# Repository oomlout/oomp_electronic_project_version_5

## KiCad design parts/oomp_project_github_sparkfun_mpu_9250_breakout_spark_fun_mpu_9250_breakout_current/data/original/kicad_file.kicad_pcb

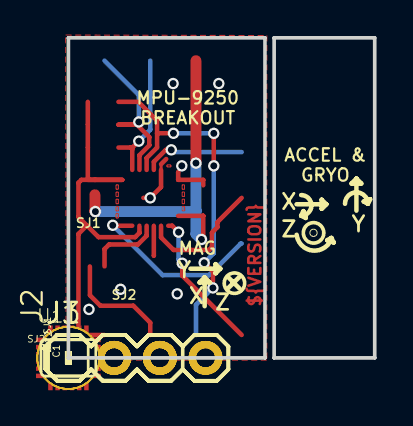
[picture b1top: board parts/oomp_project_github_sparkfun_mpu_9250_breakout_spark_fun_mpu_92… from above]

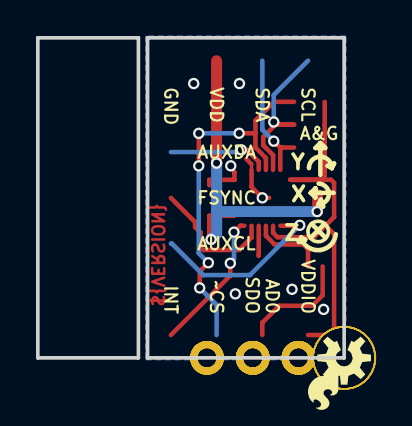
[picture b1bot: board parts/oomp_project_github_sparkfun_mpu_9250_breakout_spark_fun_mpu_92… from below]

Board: 2 copper layers, 17.0 x 17.8 mm, 18 parts (2 on the bottom side), 13 nets.

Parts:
C1, C2: 0.1uF; 0603-CAP
FID1, FID2: FIDUCIAL1X2; FIDUCIAL-1X2
FRAME1: FRAME-LETTER; CREATIVE_COMMONS
J1, J3: 1X04
J2: 1X03
LOGO1: SFE_LOGO_FLAME.1_INCH; SFE_LOGO_FLAME_.1
LOGO2: OSHW-LOGOS; OSHW-LOGO-S
R1, R2, R3: 10K; 0603-RES
SJ1: JUMPER-PAD-2-NC_BY_PASTEFULL-BOX-SILK; PAD-JUMPER-2-NC_BY_PASTE_YES_SILK_FULL_BOX
SJ2: JUMPER_PAD-3-1&2_NC_BY_PASTE; PAD-HUMPER-3-1&2_NC_BY_PASTE_YES_SILK_FULL_BOX
STANDOFF1, STANDOFF2: STAND-OFF
U1: MPU-9250; QFN24_PAD

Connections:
AD0/SDO: J3.2, SJ2.3
ADSD_STUB: SJ2.2, U1.9
AUX_CL: J2.1, U1.7
AUX_DA: J2.3, U1.21
FSYNC: J2.2, U1.11
GND: C1.2, C2.2, J1.4, SJ2.1, U1.18, U1.20, U1.CENTER
INT: J3.4, U1.12
REGOUT: C1.1, U1.10
SCL/SCLK: J1.1, R2.1, U1.23
SDA/SDI: J1.2, R1.1, U1.24
VDD: C2.1, J1.3, SJ1.1, U1.13
VDDIO: J3.1, R1.2, R2.2, R3.2, SJ1.2, U1.1, U1.8
~CS: J3.3, R3.1, U1.22

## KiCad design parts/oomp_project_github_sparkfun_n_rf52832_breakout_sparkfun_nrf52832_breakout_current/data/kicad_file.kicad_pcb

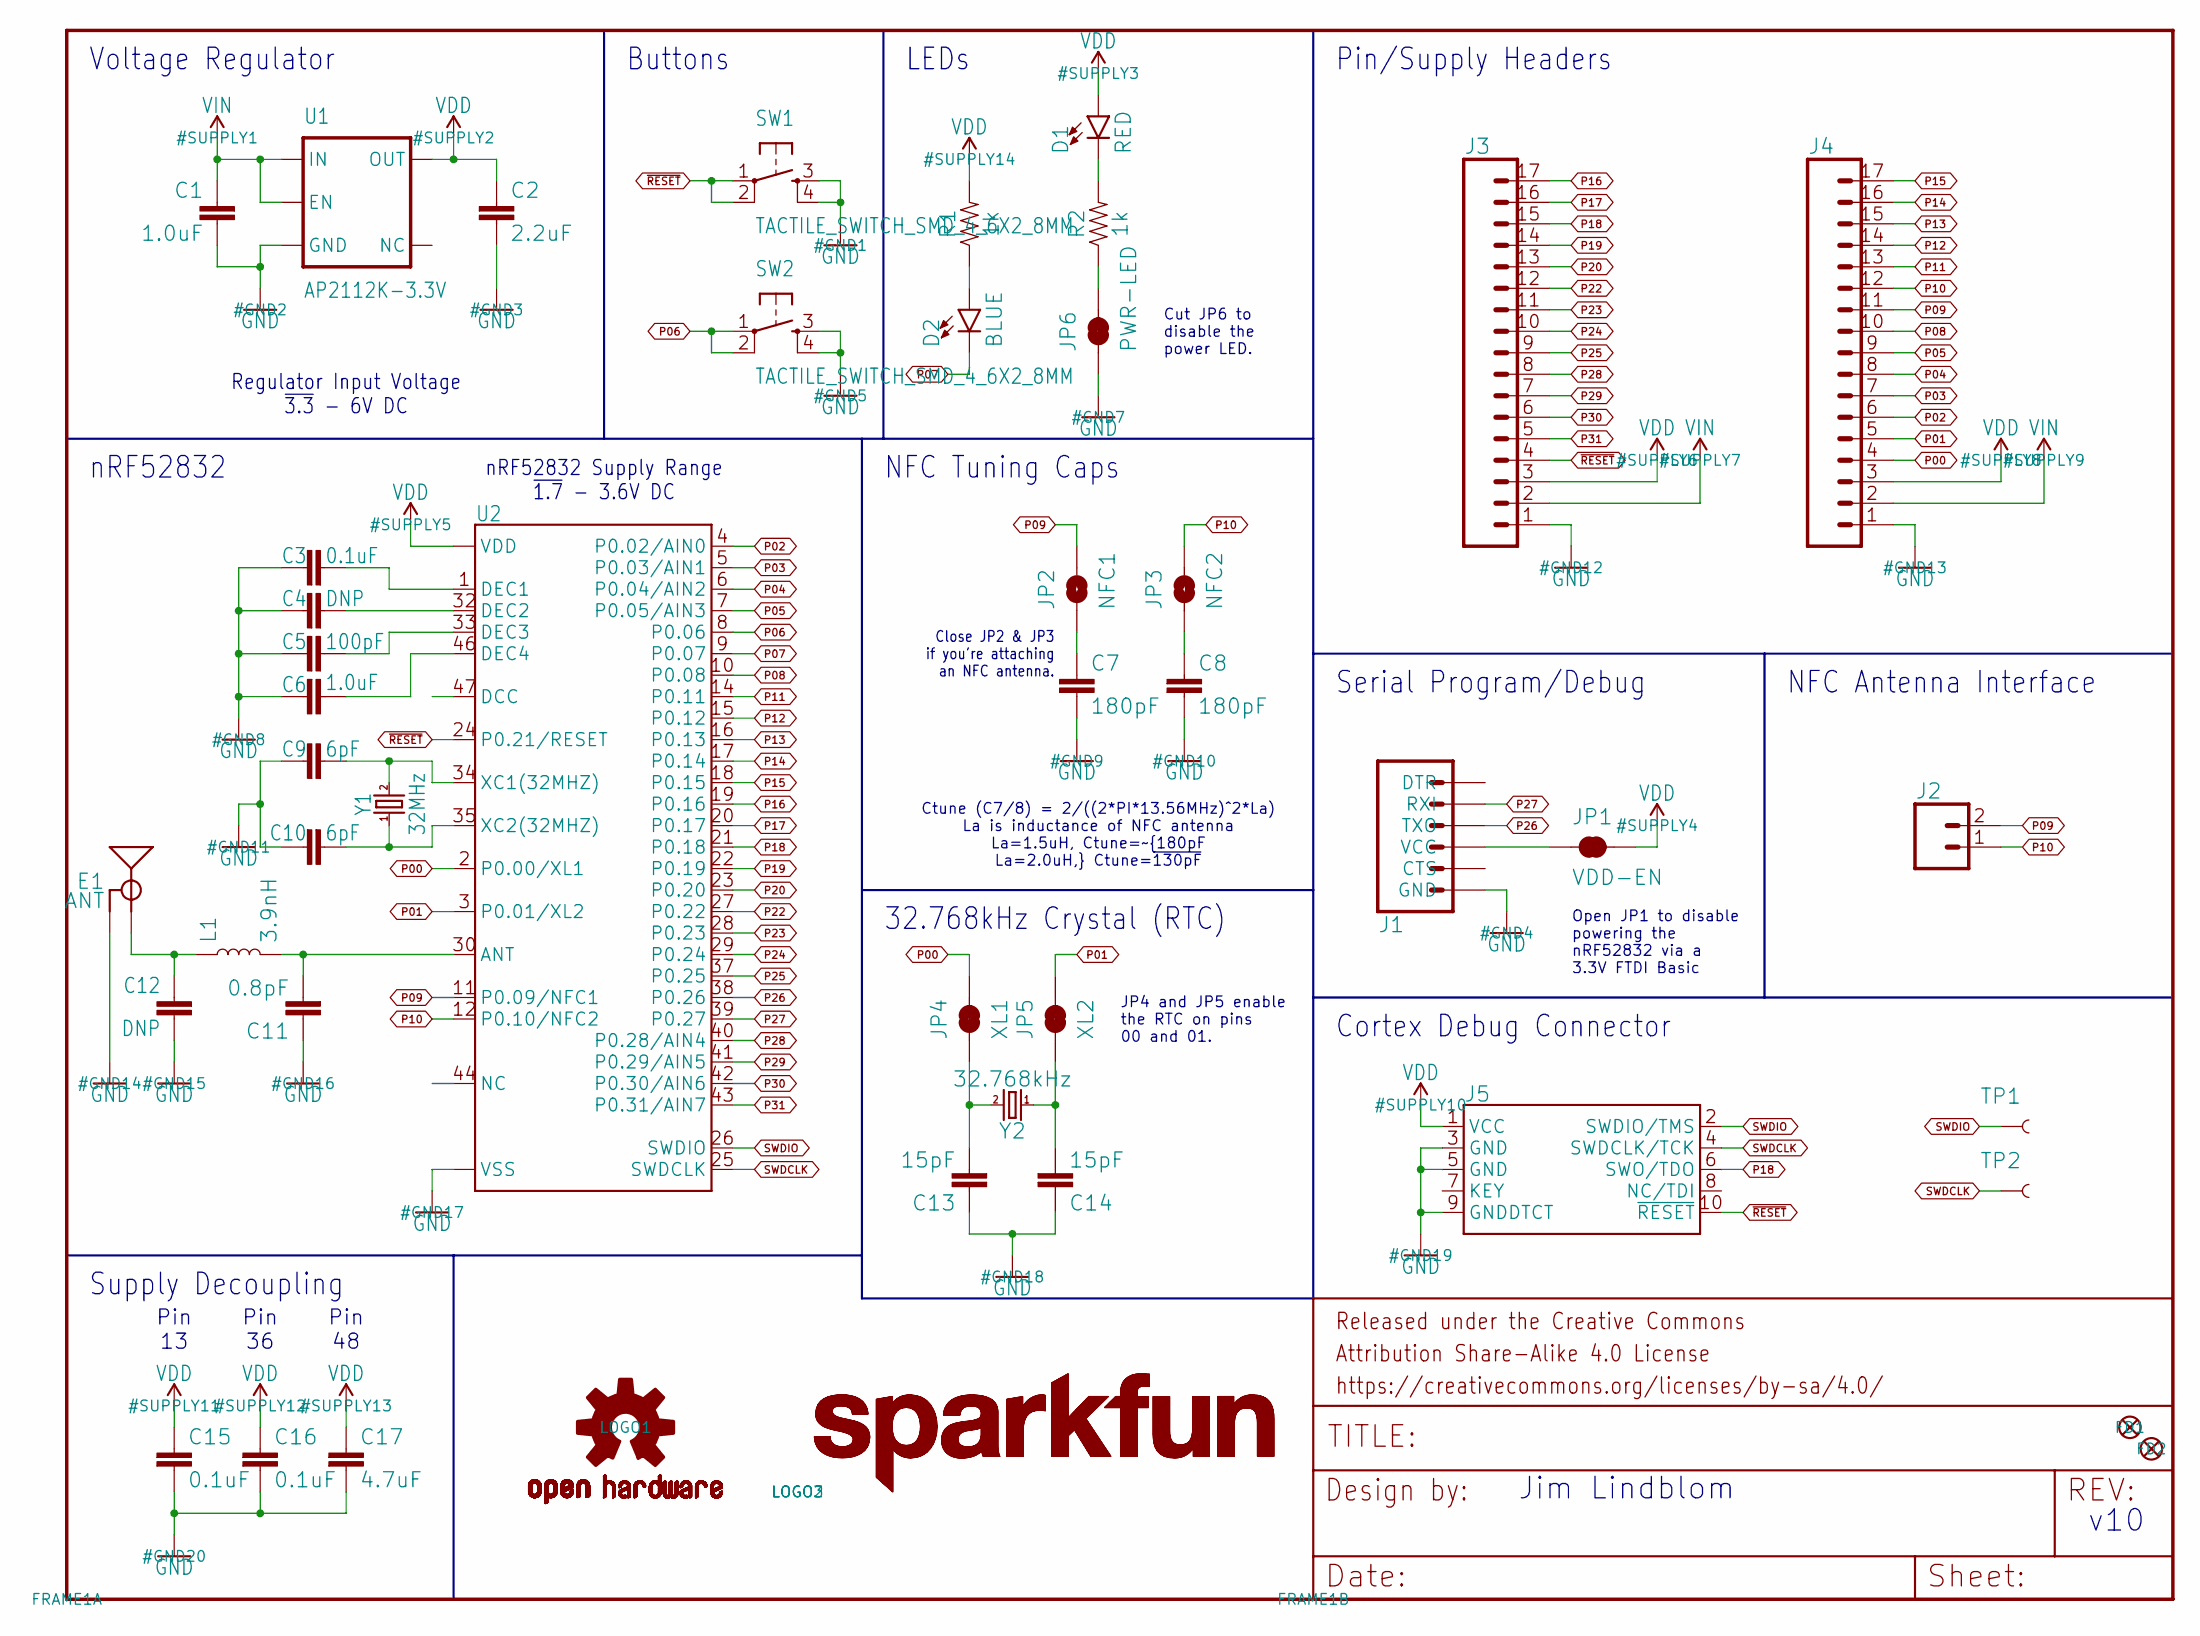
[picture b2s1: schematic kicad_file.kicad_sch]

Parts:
C1: 1.0uF; 0603
C2: 2.2uF; 0603
C3, C15, C16: 0.1uF; 0402
C4, C12: DNP; 0402
C5: 100pF; 0402
C6: 1.0uF; 0402
C7, C8: 180pF; 0603
C9, C10: 6pF; 0402
C11: 0.8pF; 0402
C13, C14: 15pF; 0402
C17: 4.7uF; 0603
D1: RED; LED-0603
D2: BLUE; LED-0603
E1: ANT; TRACE_ANTENNA_2.4GHZ_15.2MM
FD1, FD2: FIDUCIALUFIDUCIAL; FIDUCIAL-MICRO
FRAME1: FRAME-LETTER; CREATIVE_COMMONS
J1: ARDUINO_SERIAL_PROGRAMPTH; 1X06
J2: CONN_02PTH; 1X02
J3, J4: CONN_17; 1X17
J5: CORTEX_DEBUGPTH; 2X5-PTH-1.27MM
JP1: VDD-EN; SMT-JUMPER_2_NC_TRACE_SILK
JP2: NFC1; SMT-JUMPER_2_NO_SILK
JP3: NFC2; SMT-JUMPER_2_NO_SILK
JP4: XL1; PAD-JUMPER-2-NC_BY_TRACE_YES_SILK
JP5: XL2; PAD-JUMPER-2-NC_BY_TRACE_YES_SILK
JP6: PWR-LED; PAD-JUMPER-2-NC_BY_TRACE_YES_SILK
L1: 3.9nH; 0402
LOGO1: OSHW-LOGOMINI; OSHW-LOGO-MINI
LOGO2, LOGO3: SFE_LOGO_NAME.1_INCH; SFE_LOGO_NAME_.1
R1, R2: 1k; 0603
SW1, SW2: TACTILE_SWITCH_SMD_4_6X2_8MM; TACTILE_SWITCH_SMD_4.6X2.8MM
TP1, TP2: TEST-POINT3X4; PAD.03X.04
U1: AP2112K-3.3V; SOT23-5
U2: NRF52832; QFN48-6X6MM
Y1: 32MHz; CRYSTAL-SMD-2.0X1.6MM
Y2: 32.768kHz; CRYSTAL-SMD-3.2X1.5MM

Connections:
ANT: C11.2, L1.2, U2.30 (ANT)
DCC: U2.47 (DCC)
DEC1: C3.2, U2.1 (DEC1)
DEC2: C4.2, U2.32 (DEC2)
DEC3: C5.2, U2.33 (DEC3)
DEC4: C6.2, U2.46 (DEC4)
GND: C1.2, C2.2, C3.1, C4.1, C5.1, C6.1, C7.2, C8.2, C9.1, C10.2, C11.1, C12.2, C13.1, C14.1, C15.2, C16.2, C17.2, E1.GND, J1.6 (GND), J3.1, J4.1, J5.3 (GND), J5.5 (GND), J5.9 (GNDDTCT), JP6.1, SW1.3, SW1.4, SW2.3, SW2.4, U1.2 (GND), U2.31 (VSS), U2.45 (VSS), U2.EP (VSS)
unnamed: JP6.2, R2.1
unnamed: C13.2, JP4.1, Y2.P$2 (2)
unnamed: C14.2, JP5.1, Y2.P$1 (1)
unnamed: C12.1, E1.ANT (SIGNAL), L1.1
unnamed: D1.C, R2.2
unnamed: J1.4 (VCC), JP1.1
unnamed: D2.A, R1.1
NC: U2.44 (NC)
NFC1: C7.1, JP2.1
NFC2: C8.1, JP3.1
P00: J4.4, JP4.2, U2.2 (P0.00/XL1)
P01: J4.5, JP5.2, U2.3 (P0.01/XL2)
P02: J4.6, U2.4 (P0.02/AIN0)
P03: J4.7, U2.5 (P0.03/AIN1)
P04: J4.8, U2.6 (P0.04/AIN2)
P05: J4.9, U2.7 (P0.05/AIN3)
P06: SW2.1, SW2.2, U2.8 (P0.06)
P07: D2.C, U2.9 (P0.07)
P08: J4.10, U2.10 (P0.08)
P09: J2.2, J4.11, JP2.2, U2.11 (P0.09/NFC1)
P10: J2.1, J4.12, JP3.2, U2.12 (P0.10/NFC2)
P11: J4.13, U2.14 (P0.11)
P12: J4.14, U2.15 (P0.12)
P13: J4.15, U2.16 (P0.13)
P14: J4.16, U2.17 (P0.14)
P15: J4.17, U2.18 (P0.15)
P16: J3.17, U2.19 (P0.16)
P17: J3.16, U2.20 (P0.17)
P18: J3.15, J5.6 (SWO/TDO), U2.21 (P0.18)
P19: J3.14, U2.22 (P0.19)
P20: J3.13, U2.23 (P0.20)
P22: J3.12, U2.27 (P0.22)
P23: J3.11, U2.28 (P0.23)
P24: J3.10, U2.29 (P0.24)
P25: J3.9, U2.37 (P0.25)
P26: J1.3 (TXO), U2.38 (P0.26)
P27: J1.2 (RXI), U2.39 (P0.27)
P28: J3.8, U2.40 (P0.28/AIN4)
P29: J3.7, U2.41 (P0.29/AIN5)
P30: J3.6, U2.42 (P0.30/AIN6)
P31: J3.5, U2.43 (P0.31/AIN7)
SWDCLK: J5.4 (SWDCLK/TCK), TP2.P$1, U2.25 (SWDCLK)
SWDIO: J5.2 (SWDIO/TMS), TP1.P$1, U2.26 (SWDIO)
VDD: C2.1, C15.1, C16.1, C17.1, D1.A, J3.3, J4.3, J5.1 (VCC), JP1.2, R1.2, U1.5 (OUT), U2.13 (VDD), U2.36 (VDD), U2.48 (VDD)
VIN: C1.1, J3.2, J4.2, U1.1 (IN), U1.3 (EN)
XC1: C9.2, U2.34 (XC1(32MHZ)), Y1.3 (2)
XC2: C10.1, U2.35 (XC2(32MHZ)), Y1.1
~RESET: J3.4, J5.10 (~RESET), SW1.1, SW1.2, U2.24 (P0.21/RESET)

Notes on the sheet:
Pin 48
NFC Tuning Caps
Ctune (C7/8) = 2/((2*PI*13.56MHz)^2*La) La is inductance of NFC antenna La=1.5uH, Ctune=~{180pF La=2.0uH,} Ctune=~{130pF}
32.768kHz Crystal (RTC)
Jim Lindblom
Cortex Debug Connector
Close JP2 & JP3 if you're attaching an NFC antenna.
Pin 36
LEDs
Supply Decoupling
nRF52832 Supply Range ~{1.7} - 3.6V DC~{}
Voltage Regulator
Pin 13
Serial Program/Debug
Buttons
v10
Open JP1 to disable powering the nRF52832 via a 3.3V FTDI Basic
Cut JP6 to disable the power LED.
nRF52832
JP4 and JP5 enable the RTC on pins 00 and 01.
Regulator Input Voltage ~{3.3} - 6V DC~{}
Pin/Supply Headers
NFC Antenna Interface

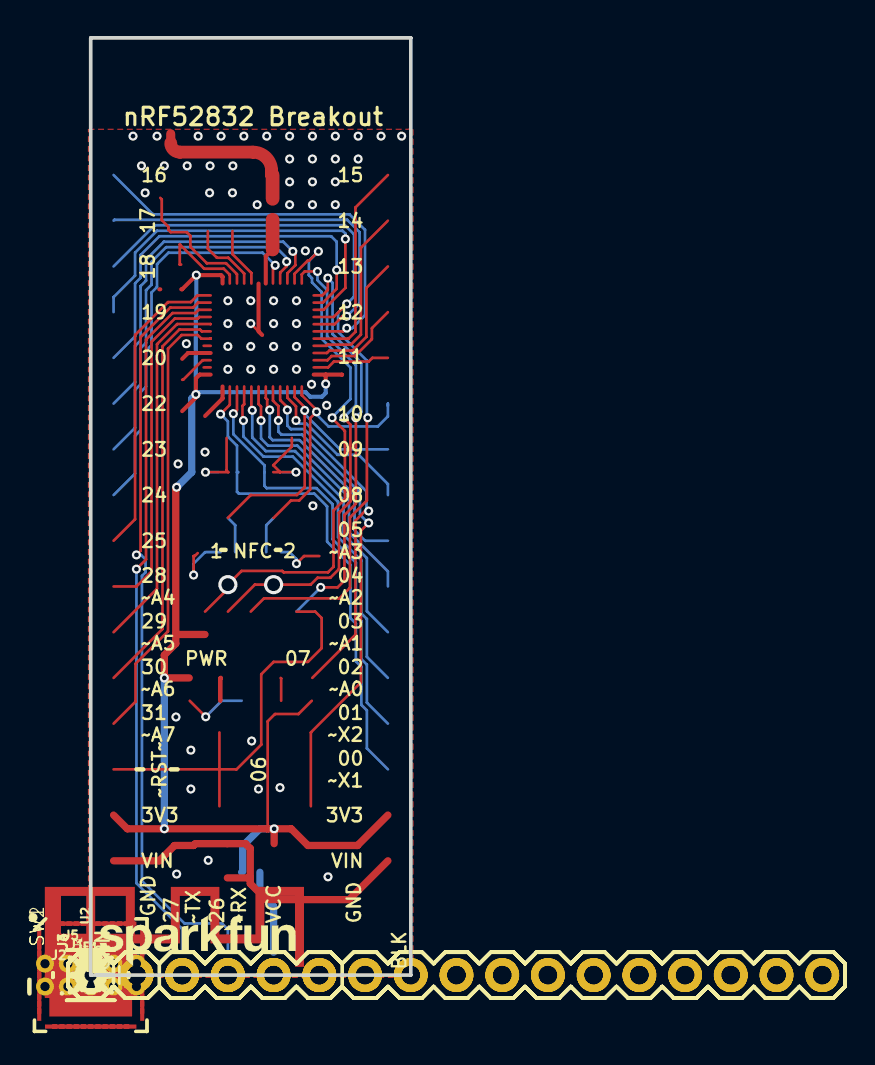
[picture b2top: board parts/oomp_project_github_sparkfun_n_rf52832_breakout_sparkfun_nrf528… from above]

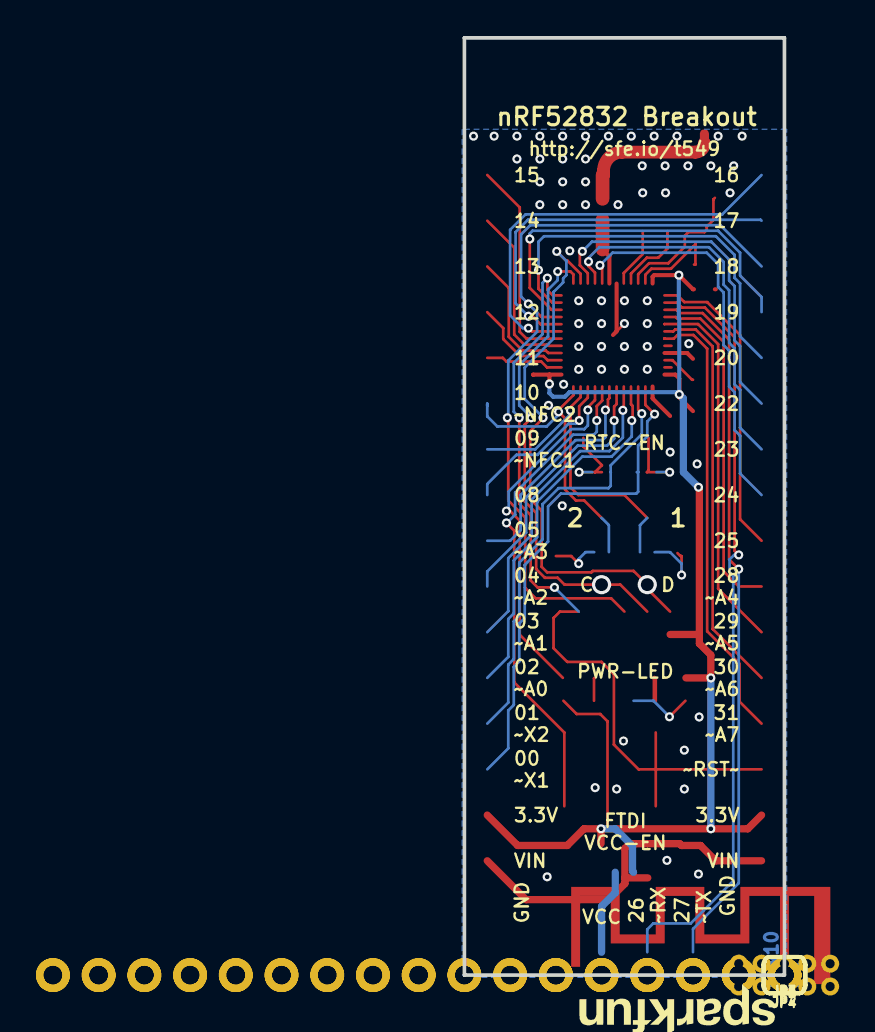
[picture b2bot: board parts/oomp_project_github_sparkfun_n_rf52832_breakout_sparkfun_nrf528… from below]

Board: 2 copper layers, 17.8 x 52.1 mm, 48 parts (9 on the bottom side), 53 nets.

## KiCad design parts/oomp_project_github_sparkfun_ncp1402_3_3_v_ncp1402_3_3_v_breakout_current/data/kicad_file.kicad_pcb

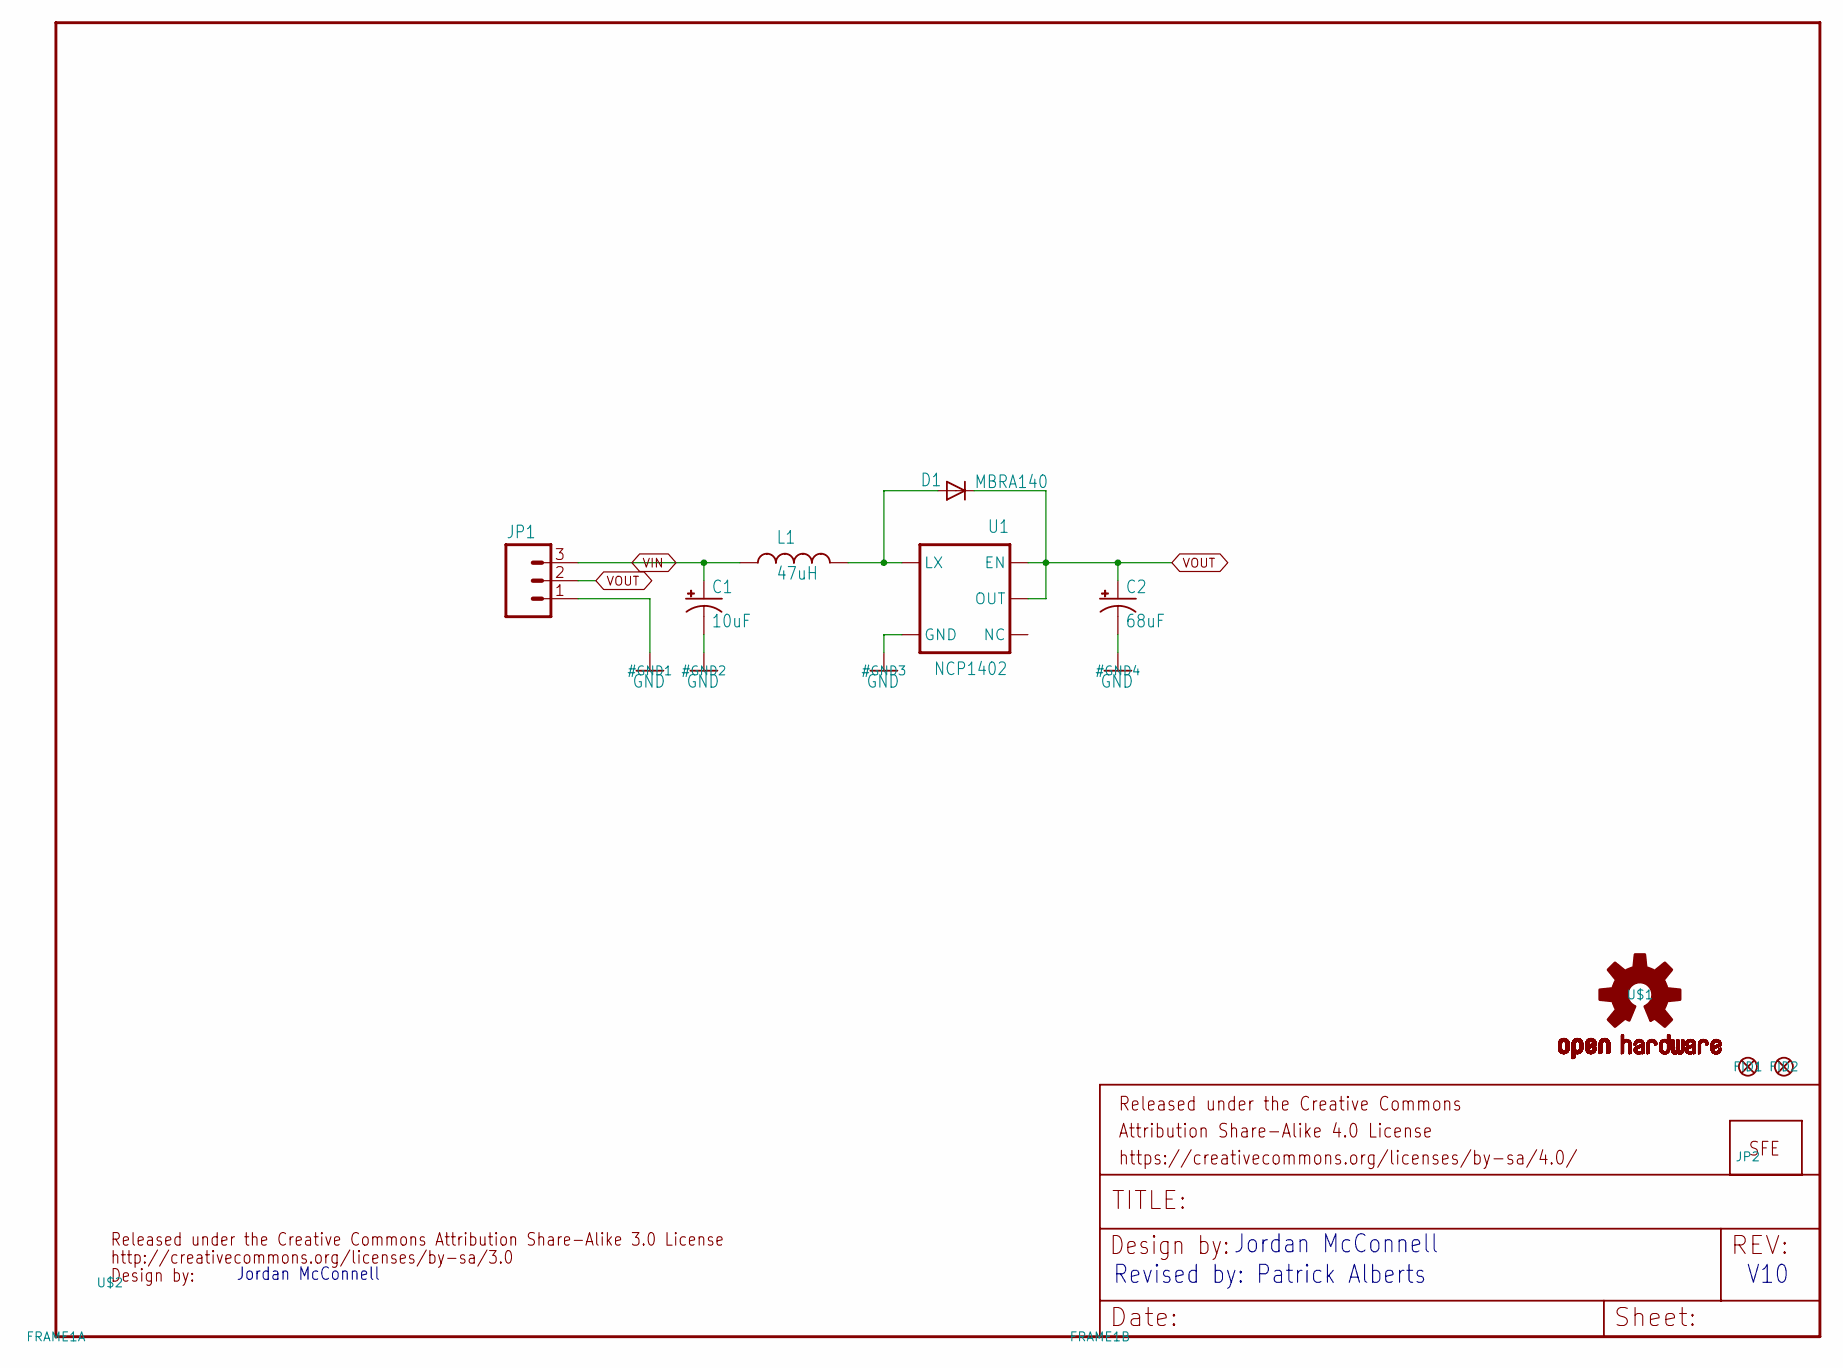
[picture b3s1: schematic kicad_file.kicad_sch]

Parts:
C1: 10uF; EIA3216
C2: 68uF; EIA3528
D1: MBRA140; SMA-DIODE
FID1, FID2: FIDUCIAL1X2; FIDUCIAL-1X2
FRAME1: FRAME-LETTER; CREATIVE_COMMONS
JP1: M03PTH; 1X03
JP2: LOGO-SFESK; SFE-LOGO-FLAME
L1: 47uH; CR54
U1: NCP1402; SOT23-5
U$1: OSHW-LOGOS; OSHW-LOGO-S
U$2: CREATIVE_COMMONS

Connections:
GND: C1.C (-), C2.C (-), JP1.1, U1.4 (GND)
unnamed: D1.A, L1.P$2 (2), U1.5 (LX)
VIN: C1.A (+), JP1.3, L1.P$1 (1)
VOUT: C2.A (+), D1.C, JP1.2, U1.1 (EN), U1.2 (OUT)

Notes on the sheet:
V10
Revised by: Patrick Alberts
Jordan McConnell

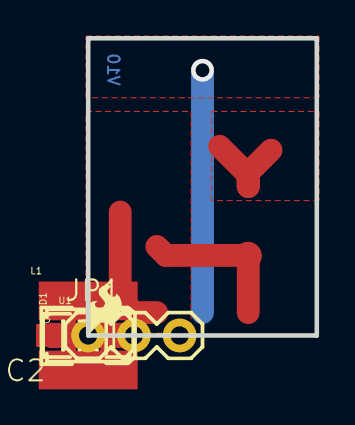
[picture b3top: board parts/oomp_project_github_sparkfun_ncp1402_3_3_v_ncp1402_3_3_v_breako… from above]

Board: 2 copper layers, 12.7 x 16.5 mm, 12 parts (1 on the bottom side), 4 nets.

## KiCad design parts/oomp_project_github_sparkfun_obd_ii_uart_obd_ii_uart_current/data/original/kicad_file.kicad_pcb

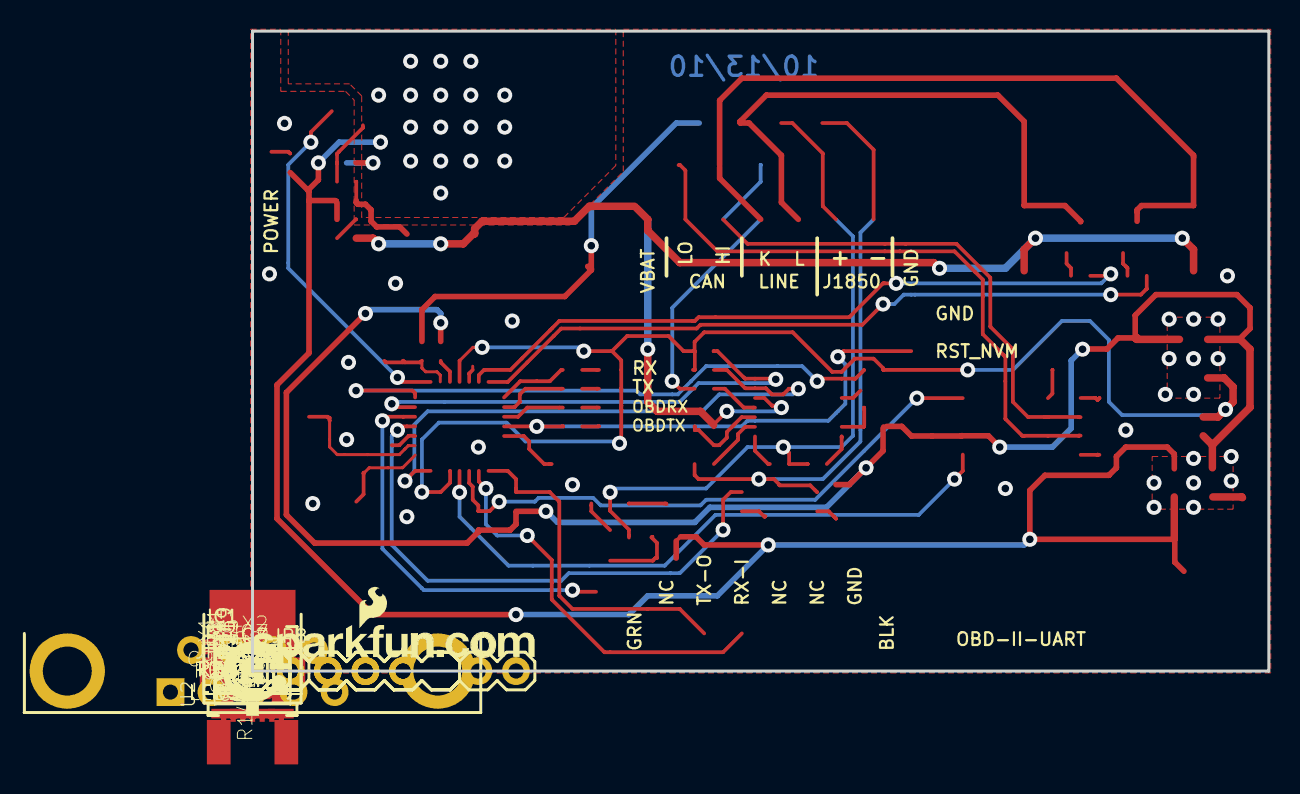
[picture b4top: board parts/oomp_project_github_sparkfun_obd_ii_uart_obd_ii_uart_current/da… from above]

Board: 2 copper layers, 68.6 x 43.2 mm, 88 parts (0 on the bottom side), 57 nets.

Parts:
C1, C5, C6, C11, C17: 1uF; 0402-CAP
C2, C3: 27pF; 0402-CAP
C4: 10uF ESR<=5; EIA3216
C7, C10, C14: 0.1uF; 0402-CAP
C8: 4.7uF; 0402-CAP
C9, C18: 10uF; EIA3216
C12, C13: 560pF; 0402-CAP
C15: 2.2uF; 0402-CAP
C16: 470pF; 0402-CAP
D1, D2, D3: BAS16; SOD-323
D4: MBRA140; SMA-DIODE
IC1: SCANTOOL; _STN_SCANTOOL_QFN-28-S
IC3: LM339PWR; TSSOP-14
IC4: MCP2551; SO-8
JP1: 1X08
JP2, JP10: FIDUCIAL1X2; FIDUCIAL-1X2
JP3: LOGO-SFENEW; SFE-NEW-WEBLOGO
JP4, JP5, JP6, JP7: STAND-OFF
JP8: DNP; FTDI_BASIC
JP9: DNP; 1X02
LED1, LED3: YELLOW; LED-0603
LED2, LED4, LED5: RED; LED-0603
Q3, Q4, Q8: MMBT2222; SOT23-3
Q7: ZXMP6A13FTA; SOT23
Q9, Q10: BSS138; SOT23-3
R1, R9, R10, R12, R18, R21, R27, R28, R29, R30, R31, R33: 10k; 0402-RES
R2, R7, R13, R32: 1k; 0402-RES
R3: 62K; 0402-RES
R4, R5, R35, R37: 330; 0402-RES
R6: 10K; 0402-RES
R8, R11: 510 0.5W; 2010
R14, R15: 100; 0402-RES
R16, R23, R25: 4.7k; 0402-RES
R17: 1.2k; 0402-RES
R19: 866; 0402-RES
R20: 240; 0402-RES
R22: 374; 0402-RES
R24, R34: 1.5k; 0402-RES
U1: 3.3V; SOT23-5
U2: V_REG_317DPACK; V-REG_DPACK
U3: 5V Reg.; SOT23-5
U$1: CREATIVE_COMMONS
U$14: OSHW-LOGO
X2: Male DB9; DB9_MALE
Y1: 16MHz; CRYSTAL-SMD-5X3

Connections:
3.3V: C1.1, C5.1, C8.1, IC1.10, IC1.25, LED1.A, LED2.A, LED3.A, LED4.A, R9.2, R18.2, R27.2, U1.5
5V: C6.1, C11.1, C15.1, C18.A, D3.2, IC4.3, R1.2, R17.2, R25.1, R34.1, U1.1, U1.3, U3.5
BATT_V: C7.1, IC1.27, R3.1, R6.2
CAN_HI: IC4.7, JP1.6, R14.2, X2.3
CAN_LO: IC4.6, JP1.7, R15.2, X2.5
CAN_RX: IC1.11, IC4.4
CAN_TX: IC1.12, IC4.1, R34.2
GND: C1.2, C2.2, C3.2, C4.C, C5.2, C6.2, C7.2, C8.2, C9.C, C10.2, C11.2, C12.2, C13.2, C14.2, C15.2, C16.2, C17.2, C18.C, D2.1, IC1.5, IC1.16, IC1.24, IC1.EXP, IC3.12, IC4.2, JP1.1, JP8.GND, JP9.2, LED5.C, Q3.2, Q4.2, Q8.2, Q9.2, Q10.2, R6.1, R16.1, R22.1, R23.1, R33.2, U1.2, U3.2, X2.1, X2.2
J1850BUS+: D1.1, JP1.3, R21.1, R28.1, R30.1, X2.7
J1850BUS+_TX: IC1.3, Q9.1
J1850BUS-: JP1.2, Q8.3, R29.1, R31.2, X2.6
J1850BUS-_TX: IC1.4, R32.1
K-LINE: JP1.5, Q4.3, R11.2, R12.1, X2.4
L-LINE: JP1.4, Q3.3, R8.2, X2.8
unnamed: IC3.7, R28.2
unnamed: IC3.6, R29.2
unnamed: Q4.1, R13.1
unnamed: Q3.1, R7.1
unnamed: IC3.5, R10.2, R33.1
unnamed: IC3.8, R21.2
unnamed: R19.2, R20.2, U2.1
unnamed: D1.2, Q7.3
unnamed: C12.1, R14.1
unnamed: IC4.8, R16.2
unnamed: IC3.9, R17.1, R23.2
unnamed: IC3.4, R12.2
unnamed: D3.1, R31.1
unnamed: Q7.1, Q9.3, R24.2
unnamed: Q10.3, R19.1, R22.2
unnamed: D2.2, R30.2
unnamed: Q8.1, R32.2
unnamed: C4.A, IC1.17
unnamed: C13.1, R15.1
unnamed: LED3.C, R4.2
unnamed: LED4.C, R5.1
unnamed: LED5.A, R2.1
unnamed: C16.1, U3.4
unnamed: LED1.C, R35.2
unnamed: LED2.C, R37.1
OSC1: C2.1, IC1.6, Y1.3
OSC2: C3.1, IC1.7, Y1.1
PWM/~VPW: IC1.28, Q10.1
PWM_RX: IC1.2, IC3.1, R27.1
RESET: IC1.26, R1.1
RST_NVM: IC1.18, JP9.1, R5.2
RX-I: IC1.13, JP8.TXO
RX-STAT: IC1.21, R35.1
TX-O: IC1.14, JP8.RXI, R25.2
TX-STAT: IC1.20, R37.2
VBAT: C14.1, D4.C, IC3.3, JP1.8, R8.1, R10.1, R11.1, U2.3
VBATT_RAW: D4.A, R3.2, X2.9
VCC: C9.A, C10.1, C17.1, Q7.2, R2.2, R20.1, R24.1, U2.4, U3.1, U3.3
~ISO_K_TX: IC1.22, R13.2
~ISO_L_TX: IC1.23, R7.2
~ISO_RX: IC1.8, IC3.2, R9.1
~OBD_RX_STATUS/PGC: IC1.19, R4.1
~VPW_RX: IC1.1, IC3.14, R18.1

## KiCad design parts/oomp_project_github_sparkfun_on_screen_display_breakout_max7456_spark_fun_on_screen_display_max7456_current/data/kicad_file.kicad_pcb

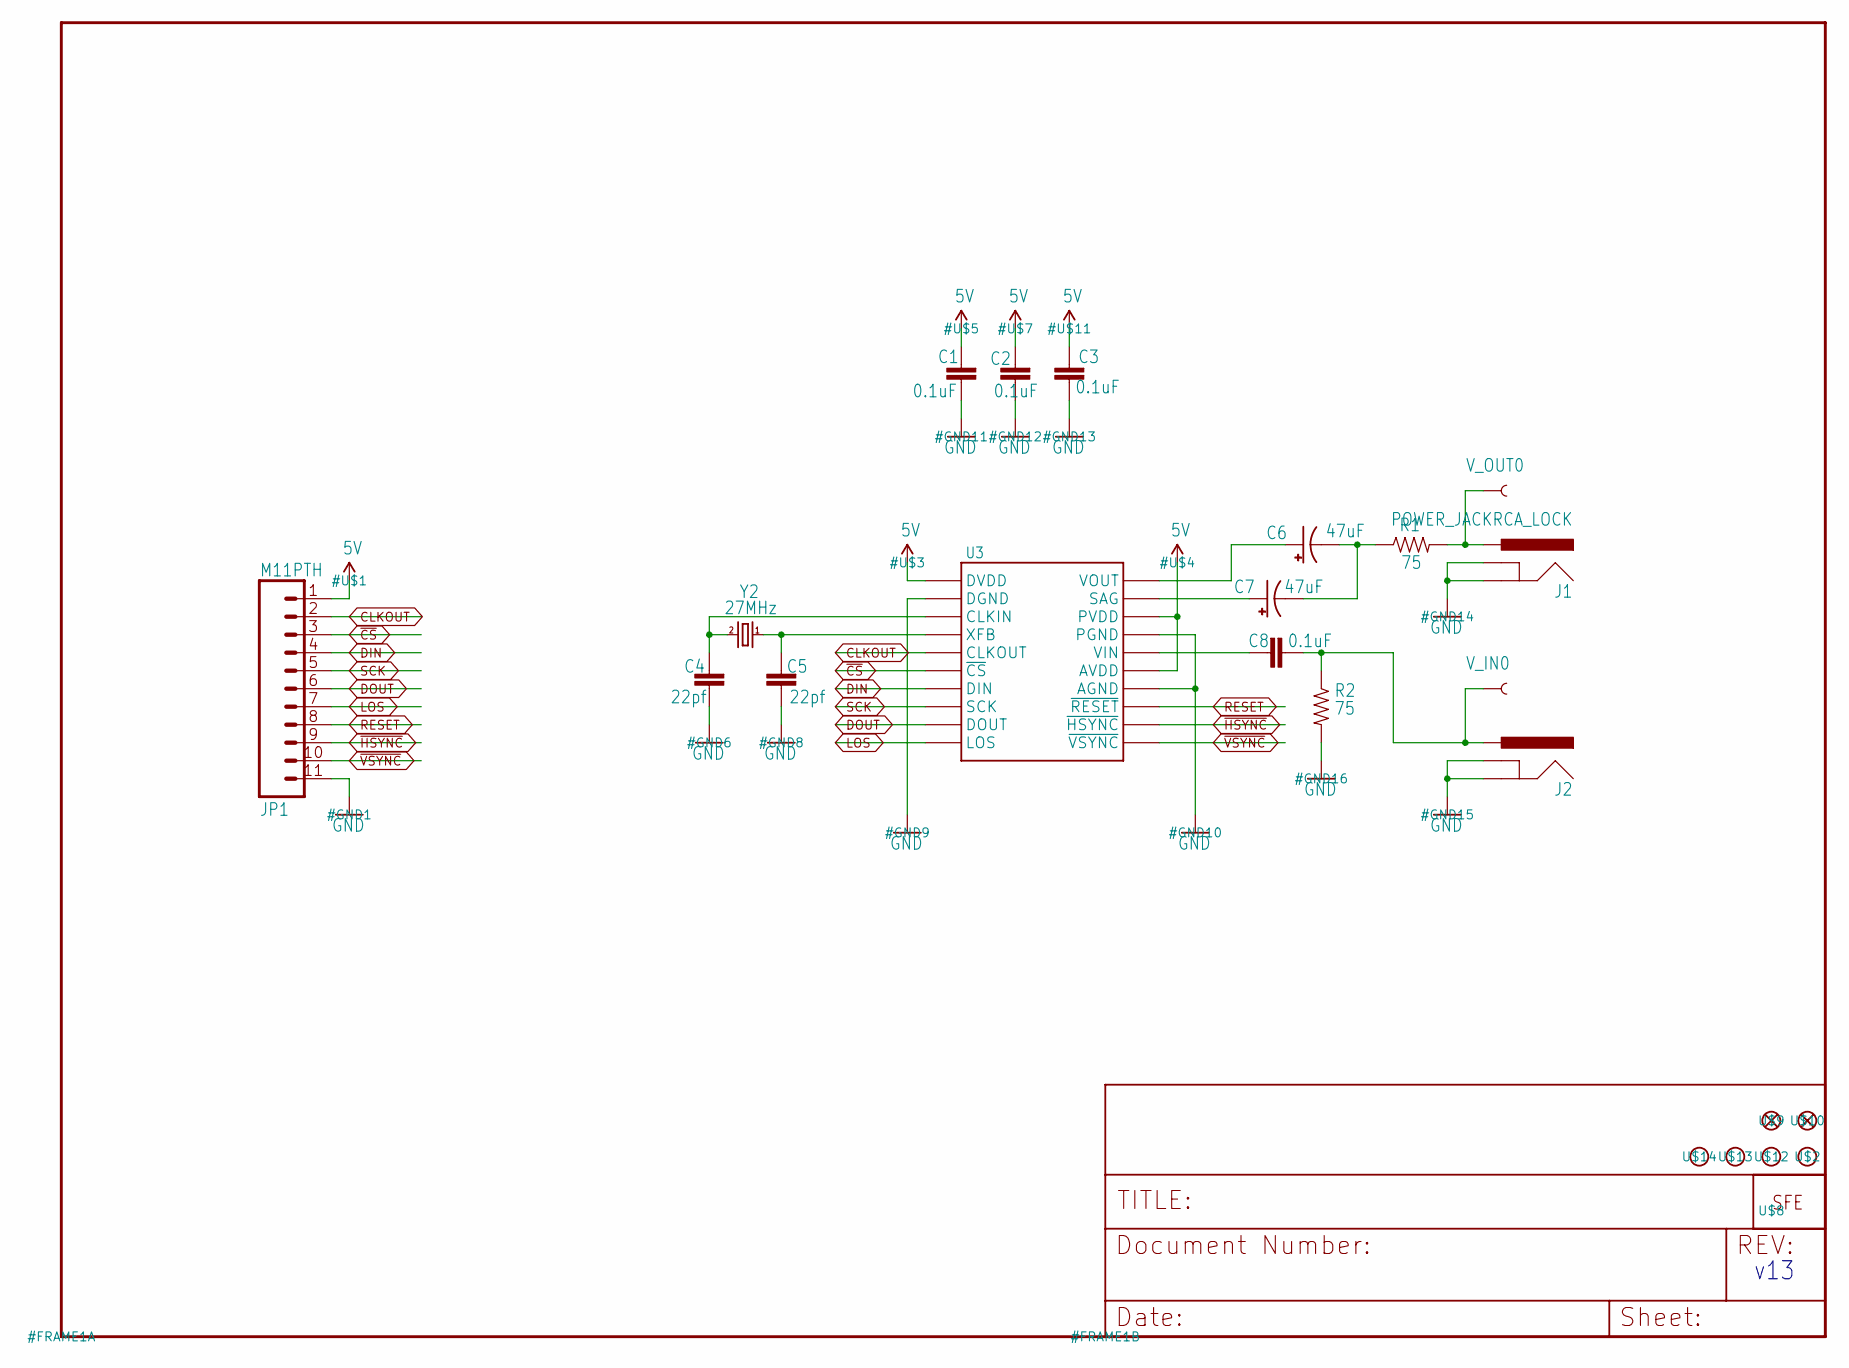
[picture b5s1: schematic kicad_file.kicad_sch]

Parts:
C1, C2, C3, C8: 0.1uF; C0402
C4, C5: 22pf; C0402
C6, C7: 47uF; EIA3528
J1, J2: POWER_JACKRCA_LOCK; RCA_LOCK
JP1: M11PTH; 1X11
R1, R2: 75; C0402
U3: MAX7456; TSSOP28
U$2, U$12, U$13, U$14: STAND-OFF
U$8: LOGO-SFENEW; SFE-NEW-WEBLOGO
U$9, U$10: FIDUCIAL1X2; FIDUCIAL-1X2
V_IN0: TEST-POINT3X5; PAD.03X.05
V_OUT0: TEST-POINT3X5; PAD.03X.05
Y2: 27MHz; CRYSTAL-SMD-5X3

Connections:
5V: C1.2, C2.2, C3.2, JP1.1, U3.3 (DVDD), U3.21 (AVDD), U3.24 (PVDD)
CLKOUT: JP1.2, U3.7 (CLKOUT)
DIN: JP1.4, U3.9 (DIN)
DOUT: JP1.6, U3.11 (DOUT)
GND: C1.1, C2.1, C3.1, C4.1, C5.1, J1.BARREL (GND), J1.SPRING (GNDBREAK), J2.BARREL (GND), J2.SPRING (GNDBREAK), JP1.11, R2.2, U3.4 (DGND), U3.20 (AGND), U3.23 (PGND)
LOS: JP1.7, U3.12 (LOS)
unnamed: C4.2, U3.5 (CLKIN), Y2.3 (2)
unnamed: C5.2, U3.6 (XFB), Y2.1
unnamed: C6.C (-), C7.C (-), R1.1
unnamed: C7.A (+), U3.25 (SAG)
unnamed: C6.A (+), U3.26 (VOUT)
unnamed: J1.BREAK (PWR), R1.2, V_OUT0.P$1
unnamed: C8.2, U3.22 (VIN)
unnamed: C8.1, J2.BREAK (PWR), R2.1, V_IN0.P$1
RESET: JP1.8, U3.19 (~RESET)
SCK: JP1.5, U3.10 (SCK)
~CS: JP1.3, U3.8 (~CS)
~HSYNC: JP1.9, U3.18 (~HSYNC)
~VSYNC: JP1.10, U3.17 (~VSYNC)

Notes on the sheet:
v13

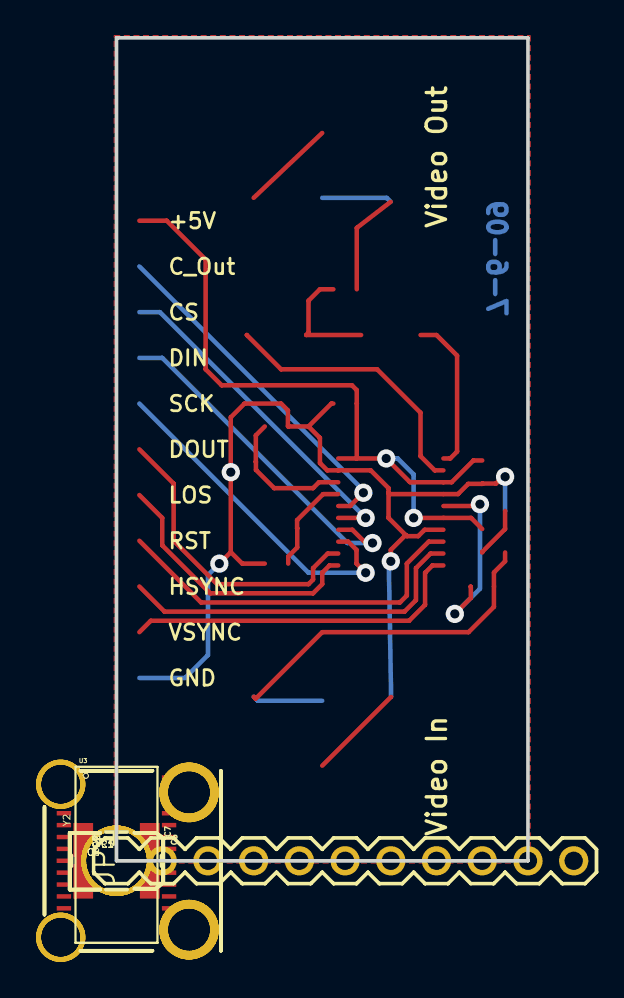
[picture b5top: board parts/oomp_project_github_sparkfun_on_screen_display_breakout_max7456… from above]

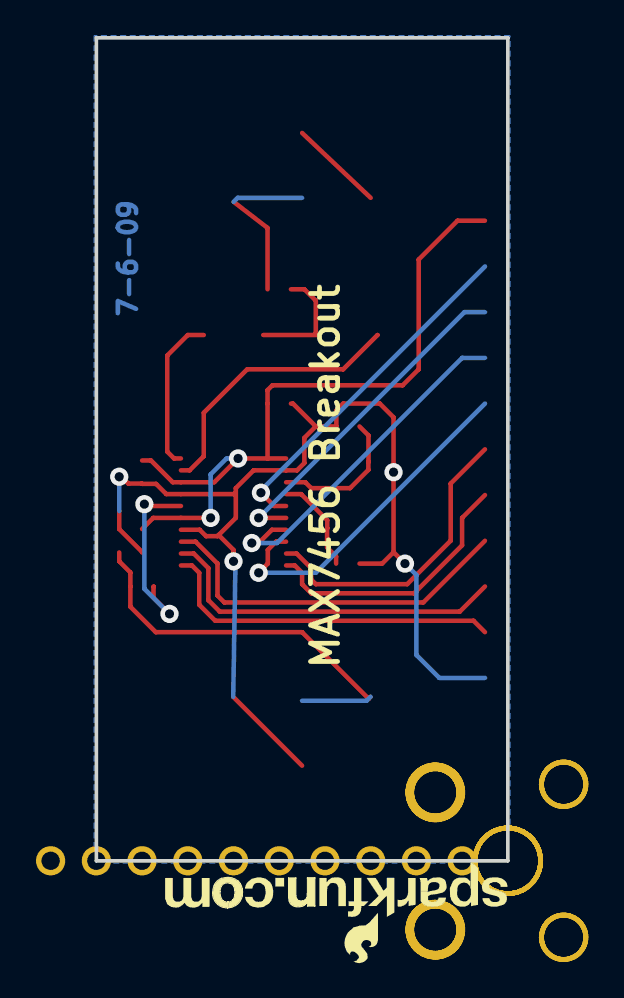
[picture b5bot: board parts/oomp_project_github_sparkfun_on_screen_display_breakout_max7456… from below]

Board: 2 copper layers, 22.9 x 45.7 mm, 24 parts (3 on the bottom side), 19 nets.

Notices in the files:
parts/oomp_project_github_sparkfun_n_rf52832_breakout_sparkfun_nrf52832_breakout_current/data/kicad_file.kicad_sch:
Released under the Creative Commons
https://creativecommons.org/licenses/by-sa/4.0
parts/oomp_project_github_sparkfun_ncp1402_3_3_v_ncp1402_3_3_v_breakout_current/data/kicad_file.kicad_sch:
Released under the Creative Commons Attribution Share-Alike 3.0 License
http://creativecommons.org/licenses/by-sa/3.0
parts and their libraries:
Released under the Creative Commons Attribution Share-Alike 4.0 License
